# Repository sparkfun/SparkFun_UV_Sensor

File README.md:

SparkFun UV Sensor (Qwiic) - VEML6075
========================================

[*SparkFun UV Sensor (Qwiic) - VEML6075 (SEN-15089)*](https://www.sparkfun.com/products/15089)

Need to apply some sunscreen? SPF 15? SPF 50? SPF 5000? It's time to consult the Qwiic VEML6075 UV sensor!

The **VEML6075** can detect the intensity of UVA (~365nm) and UVB (~330nm) waves. With a quick calculation, those values can be used to generate a standardized **UV index** -- a value from 0 to 11+ which indicates the relative strength of UV irradiance. Seeing a UVI above 6-7? Find some shade, or slather on that sun screen!

The VEML6075 features a simple I<sup>2</sup>C interface, so we stuck it on a [Qwiic](https://www.sparkfun.com/qwiic)-compatible board. This board requires no voltage translation, no figuring out which pin is SDA or SCL; just plug it in and go!

Check out our [SparkFun_VEML6075_Arduino_Library repo](https://github.com/sparkfun/SparkFun_VEML6075_Arduino_Library) for a simple Arduino library -- there's example code to configure the sensor, read its UVA and UVB outputs, and generate a UV index output. Stay safe out there this summer!

SparkFun labored with love to create this code. Feel like supporting open source hardware? 
Buy a [breakout board](https://www.sparkfun.com/products/15089) from SparkFun!

Repository Contents
-------------------

* **/Documents** - Datasheets
* **/Hardware** - Eagle design files (.brd, .sch)
* **/Production** - Production panel files (.brd)

Documentation
--------------
* **[Installing an Arduino Library Guide](https://learn.sparkfun.com/tutorials/installing-an-arduino-library)** - Basic information on how to install an Arduino library.
* **[Library](https://github.com/sparkfun/SparkFun_VEML6075_Arduino_Library)** - Arduino library.
* **[Hookup Guide](https://learn.sparkfun.com/tutorials/qwiic-uv-sensor-veml6075-hookup-guide)** - Basic hookup guide.

Product Versions
----------------
* [SEN-15089](https://www.sparkfun.com/products/15089)- SparkFun Red Version
* [SPX-14748](https://www.sparkfun.com/products/14748)- SparkX Version

License Information
-------------------

This product is _**open source**_! 

Various bits of the code have different licenses applied. Please use, reuse, and modify these files as you see fit. Please maintain attribution to SparkFun Electronics and release any derivative under the same license.

If you have any questions or concerns on licensing, please contact techsupport@sparkfun.com. 

Distributed as-is; no warranty is given.

- Your friends at SparkFun.

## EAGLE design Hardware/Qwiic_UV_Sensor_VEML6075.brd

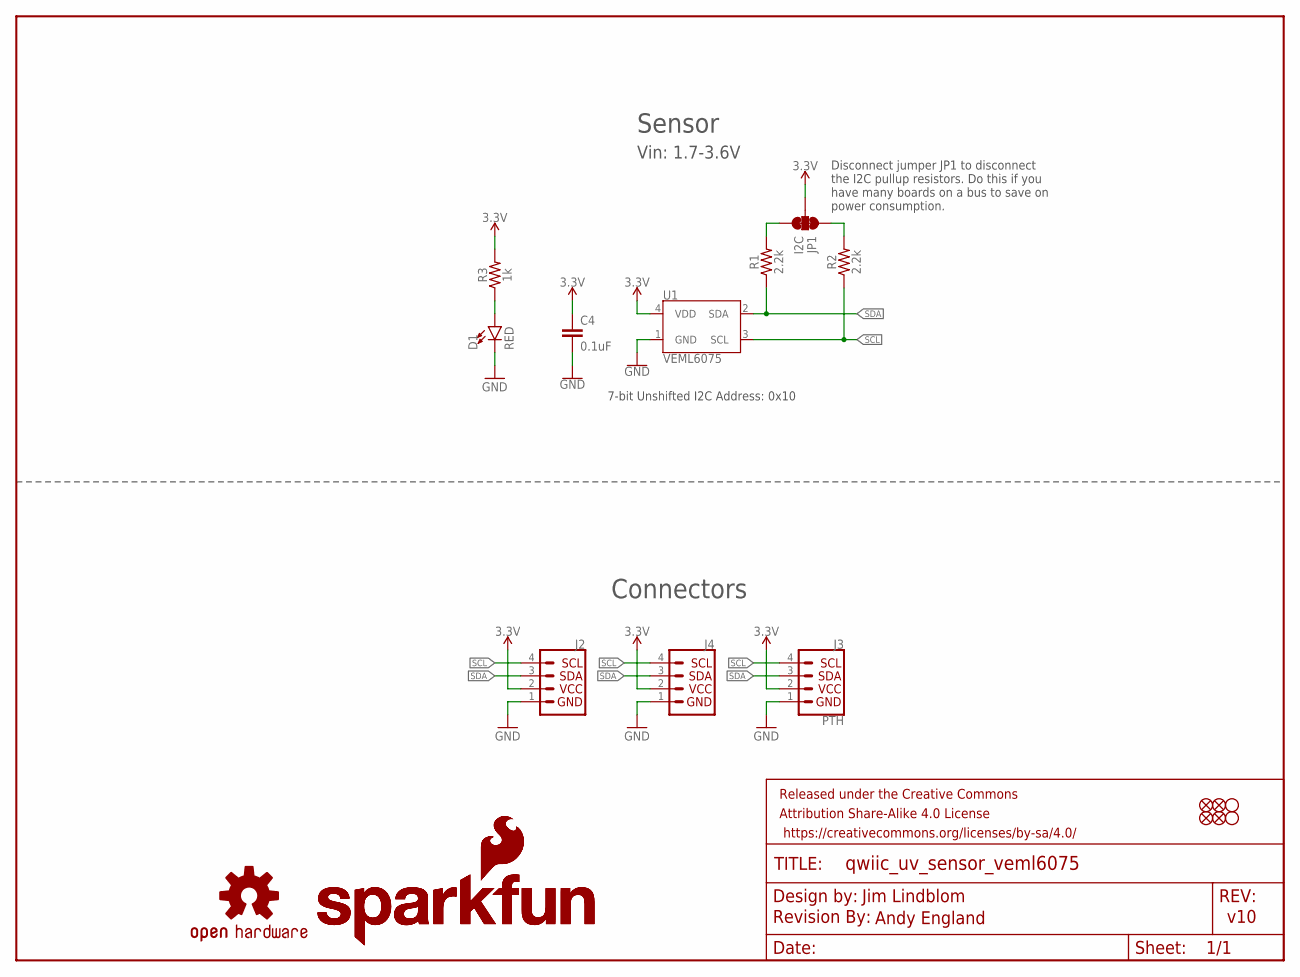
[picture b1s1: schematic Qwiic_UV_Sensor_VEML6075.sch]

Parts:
C4: 0.1uF; 0603
D1: RED; LED-0603
FRAME1: FRAME-LETTER; CREATIVE_COMMONS
J2, J4: QWIIC_CONNECTORJS-1MM; 1X04_1MM_RA
J3: PTH; 1X04_NO_SILK
JP1: I2C; SMT-JUMPER_3_2-NC_TRACE_SILK
JP2, JP5, JP6, JP7: FIDUCIALUFIDUCIAL; MICRO-FIDUCIAL
JP3, JP4: STAND-OFF
LOGO1: OSHW-LOGOMINI; OSHW-LOGO-MINI
LOGO2: REVISION
R1, R2: 2.2k; 0603
R3: 1k; 0603
U1: VEML6075; VEML6075_A3OP
U$1, U$2: SFE_LOGO_NAME_FLAME.1_INCH; SFE_LOGO_NAME_FLAME_.1

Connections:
3.3V: C4.1, J2.2, J3.2 (VCC), J4.2, JP1.2, R3.2, U1.4 (VDD)
GND: C4.2, D1.C, J2.1, J3.1 (GND), J4.1, U1.1 (GND)
unnamed: D1.A, R3.1
unnamed: JP1.3, R1.2
unnamed: JP1.1, R2.2
SCL: J2.4, J3.4 (SCL), J4.4, R2.1, U1.3 (SCL)
SDA: J2.3, J3.3 (SDA), J4.3, R1.1, U1.2 (SDA)

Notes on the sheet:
7-bit Unshifted I2C Address: 0x10
v10
Sensor
Connectors
Jim Lindblom
Andy England
Vin: 1.7-3.6V
Disconnect jumper JP1 to disconnect the I2C pullup resistors. Do this if you have many boards on a bus to save on power consumption.

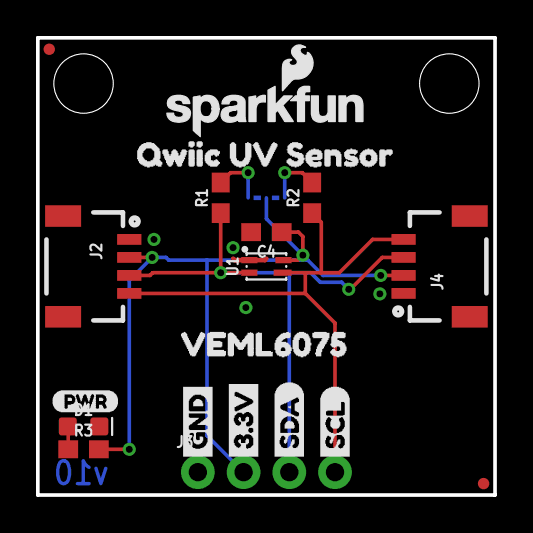
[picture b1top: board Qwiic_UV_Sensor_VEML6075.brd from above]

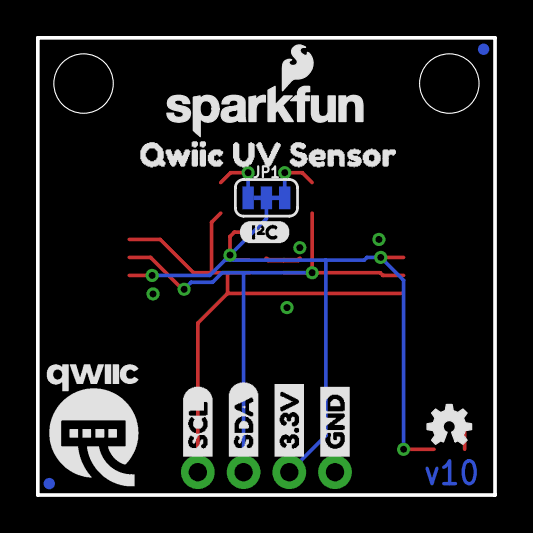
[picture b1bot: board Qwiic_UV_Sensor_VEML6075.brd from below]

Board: 2 copper layers, 25.4 x 25.4 mm, 35 parts (12 on the bottom side), 7 nets.

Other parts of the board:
U$3: QWIIC-LOGO-MEDIUM
U$4, U$22: GND1
U$5, U$11: QWIIC_UV_SENSOR1
U$6: _VEML60750
U$7, U$21: 3#3V2
U$8, U$27: SDA8
U$9, U$26: SCL9
U$10: I_SUPER2_C-()-03
U$16: PWR-()-03

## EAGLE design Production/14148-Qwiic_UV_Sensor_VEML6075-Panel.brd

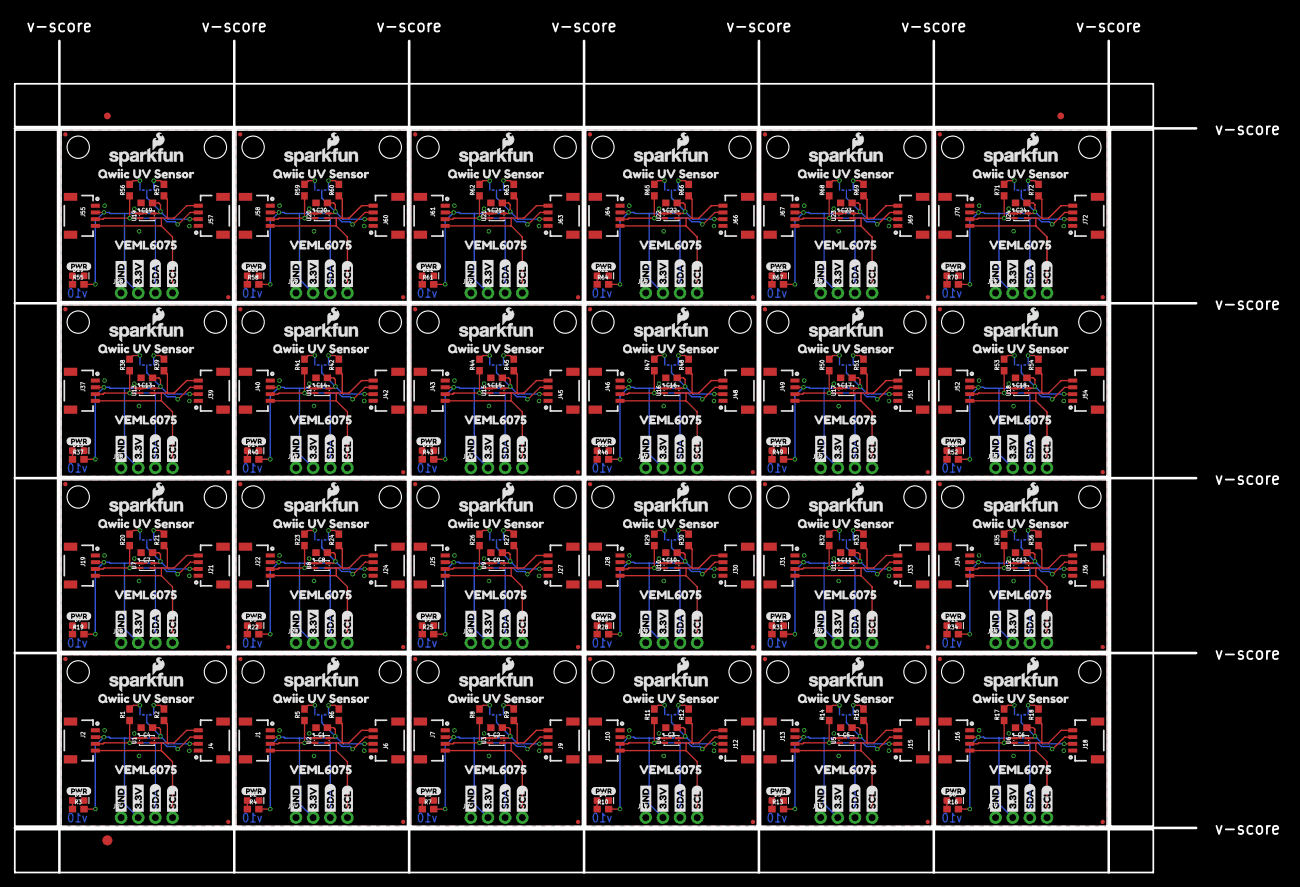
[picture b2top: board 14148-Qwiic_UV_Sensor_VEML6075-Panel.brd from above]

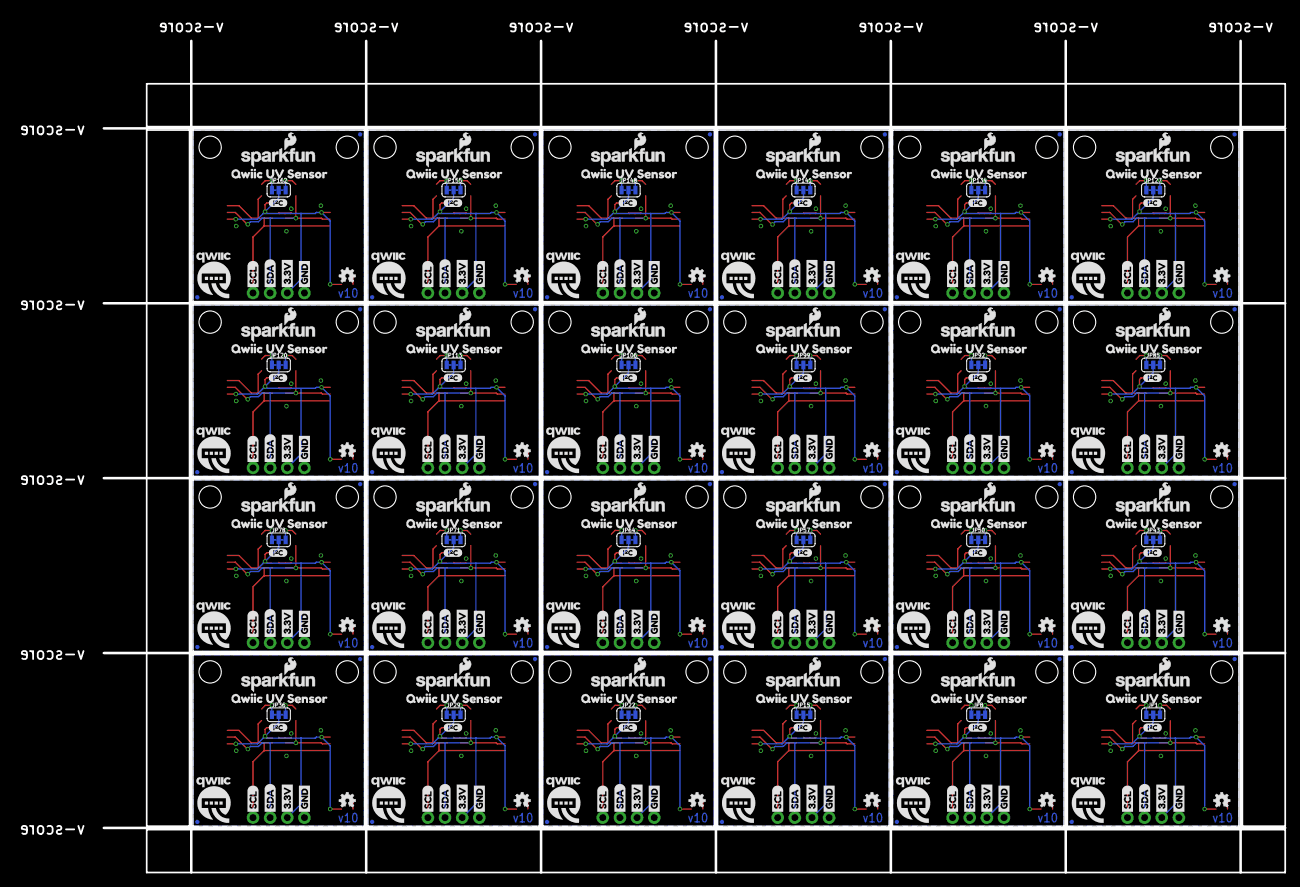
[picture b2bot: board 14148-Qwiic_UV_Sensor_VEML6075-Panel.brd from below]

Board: 2 copper layers, 175.0 x 123.2 mm, 795 parts (288 on the bottom side), 168 nets.

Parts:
C1, C2, C3, C4, C5, C6, C7, C8, C9, C10, C11, C12, C13, C14, C15, C16, C17, C18, C19, C20, C21, C22, C23, C24: 0.1uF; 0603
D1, D2, D3, D4, D5, D6, D7, D8, D9, D10, D11, D12, D13, D14, D15, D16, D17, D18, D19, D20, D21, D22, D23, D24: RED; LED-0603
E$1, E$2: FIDUCIAL-1X2
E$3: FIDUCIAL-1.5X3
J1, J2, J4, J6, J7, J9, J10, J12, J13, J15, J16, J18, J19, J21, J22, J24, J25, J27, J28, J30, J31, J33, J34, J36, J37, J39, J40, J42, J43, J45, J46, J48, J49, J51, J52, J54, J55, J57, J58, J60, J61, J63, J64, J66, J67, J69, J70, J72: 1X04_1MM_RA
J3, J5, J8, J11, J14, J17, J20, J23, J26, J29, J32, J35, J38, J41, J44, J47, J50, J53, J56, J59, J62, J65, J68, J71: PTH; 1X04_NO_SILK
JP1, JP8, JP15, JP22, JP29, JP36, JP43, JP50, JP57, JP64, JP71, JP78, JP85, JP92, JP99, JP106, JP113, JP120, JP127, JP134, JP141, JP148, JP155, JP162: I2C; SMT-JUMPER_3_2-NC_TRACE_SILK
JP2, JP5, JP6, JP7, JP11, JP12, JP13, JP14, JP18, JP19, JP20, JP21, JP25, JP26, JP27, JP28, JP32, JP33, JP34, JP35, JP39, JP40, JP41, JP42, JP46, JP47, JP48, JP49, JP53, JP54, JP55, JP56, JP60, JP61, JP62, JP63, JP67, JP68, JP69, JP70, JP74, JP75, JP76, JP77, JP81, JP82, JP83, JP84, JP88, JP89, JP90, JP91, JP95, JP96, JP97, JP98, JP102, JP103, JP104, JP105, JP109, JP110, JP111, JP112, JP116, JP117, JP118, JP119, JP123, JP124, JP125, JP126, JP130, JP131, JP132, JP133, JP137, JP138, JP139, JP140, JP144, JP145, JP146, JP147, JP151, JP152, JP153, JP154, JP158, JP159, JP160, JP161, JP165, JP166, JP167, JP168: FIDUCIALUFIDUCIAL; MICRO-FIDUCIAL
JP3, JP4, JP9, JP10, JP16, JP17, JP23, JP24, JP30, JP31, JP37, JP38, JP44, JP45, JP51, JP52, JP58, JP59, JP65, JP66, JP72, JP73, JP79, JP80, JP86, JP87, JP93, JP94, JP100, JP101, JP107, JP108, JP114, JP115, JP121, JP122, JP128, JP129, JP135, JP136, JP142, JP143, JP149, JP150, JP156, JP157, JP163, JP164: STAND-OFF
LOGO1, LOGO2, LOGO3, LOGO4, LOGO5, LOGO6, LOGO7, LOGO8, LOGO9, LOGO10, LOGO11, LOGO12, LOGO13, LOGO14, LOGO15, LOGO16, LOGO17, LOGO18, LOGO19, LOGO20, LOGO21, LOGO22, LOGO23, LOGO24: OSHW-LOGOMINI; OSHW-LOGO-MINI
R1, R2, R5, R6, R8, R9, R11, R12, R14, R15, R17, R18, R20, R21, R23, R24, R26, R27, R29, R30, R32, R33, R35, R36, R38, R39, R41, R42, R44, R45, R47, R48, R50, R51, R53, R54, R56, R57, R59, R60, R62, R63, R65, R66, R68, R69, R71, R72: 2.2k; 0603
R3, R4, R7, R10, R13, R16, R19, R22, R25, R28, R31, R34, R37, R40, R43, R46, R49, R52, R55, R58, R61, R64, R67, R70: 1k; 0603
U1, U2, U3, U4, U5, U6, U7, U8, U9, U10, U11, U12, U13, U14, U15, U16, U17, U18, U19, U20, U21, U22, U23, U24: VEML6075; VEML6075_A3OP
U$1, U$2, U$12, U$13, U$33, U$34, U$49, U$50, U$65, U$66, U$81, U$82, U$97, U$98, U$113, U$114, U$129, U$130, U$145, U$146, U$161, U$162, U$177, U$178, U$193, U$194, U$209, U$210, U$225, U$226, U$241, U$242, U$257, U$258, U$273, U$274, U$289, U$290, U$305, U$306, U$321, U$322, U$337, U$338, U$353, U$354, U$369, U$370: SFE_LOGO_NAME_FLAME.1_INCH; SFE_LOGO_NAME_FLAME_.1
U$3, U$14, U$35, U$51, U$67, U$83, U$99, U$115, U$131, U$147, U$163, U$179, U$195, U$211, U$227, U$243, U$259, U$275, U$291, U$307, U$323, U$339, U$355, U$371: QWIIC-LOGO-MEDIUM
U$4, U$17, U$22, U$28, U$37, U$44, U$53, U$60, U$69, U$76, U$85, U$92, U$101, U$108, U$117, U$124, U$133, U$140, U$149, U$156, U$165, U$172, U$181, U$188, U$197, U$204, U$213, U$220, U$229, U$236, U$245, U$252, U$261, U$268, U$277, U$284, U$293, U$300, U$309, U$316, U$325, U$332, U$341, U$348, U$357, U$364, U$373, U$380: GND1
U$5, U$11, U$25, U$32, U$43, U$48, U$59, U$64, U$75, U$80, U$91, U$96, U$107, U$112, U$123, U$128, U$139, U$144, U$155, U$160, U$171, U$176, U$187, U$192, U$203, U$208, U$219, U$224, U$235, U$240, U$251, U$256, U$267, U$272, U$283, U$288, U$299, U$304, U$315, U$320, U$331, U$336, U$347, U$352, U$363, U$368, U$379, U$384: QWIIC_UV_SENSOR1
U$6, U$24, U$42, U$58, U$74, U$90, U$106, U$122, U$138, U$154, U$170, U$186, U$202, U$218, U$234, U$250, U$266, U$282, U$298, U$314, U$330, U$346, U$362, U$378: _VEML60750
U$7, U$15, U$21, U$29, U$36, U$45, U$52, U$61, U$68, U$77, U$84, U$93, U$100, U$109, U$116, U$125, U$132, U$141, U$148, U$157, U$164, U$173, U$180, U$189, U$196, U$205, U$212, U$221, U$228, U$237, U$244, U$253, U$260, U$269, U$276, U$285, U$292, U$301, U$308, U$317, U$324, U$333, U$340, U$349, U$356, U$365, U$372, U$381: 3#3V2
U$8, U$19, U$27, U$30, U$39, U$46, U$55, U$62, U$71, U$78, U$87, U$94, U$103, U$110, U$119, U$126, U$135, U$142, U$151, U$158, U$167, U$174, U$183, U$190, U$199, U$206, U$215, U$222, U$231, U$238, U$247, U$254, U$263, U$270, U$279, U$286, U$295, U$302, U$311, U$318, U$327, U$334, U$343, U$350, U$359, U$366, U$375, U$382: SDA8
U$9, U$18, U$26, U$31, U$38, U$47, U$54, U$63, U$70, U$79, U$86, U$95, U$102, U$111, U$118, U$127, U$134, U$143, U$150, U$159, U$166, U$175, U$182, U$191, U$198, U$207, U$214, U$223, U$230, U$239, U$246, U$255, U$262, U$271, U$278, U$287, U$294, U$303, U$310, U$319, U$326, U$335, U$342, U$351, U$358, U$367, U$374, U$383: SCL9
U$10, U$20, U$40, U$56, U$72, U$88, U$104, U$120, U$136, U$152, U$168, U$184, U$200, U$216, U$232, U$248, U$264, U$280, U$296, U$312, U$328, U$344, U$360, U$376: I_SUPER2_C-()-03
U$16, U$23, U$41, U$57, U$73, U$89, U$105, U$121, U$137, U$153, U$169, U$185, U$201, U$217, U$233, U$249, U$265, U$281, U$297, U$313, U$329, U$345, U$361, U$377: PWR-()-03

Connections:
3.3V: C4.1, J2.2, J3.2, J4.2, JP1.2, R3.2, U1.4
3.3V1: C1.1, J1.2, J5.2, J6.2, JP8.2, R4.2, U2.4
3.3V2: C2.1, J7.2, J8.2, J9.2, JP15.2, R7.2, U3.4
3.3V3: C3.1, J10.2, J11.2, J12.2, JP22.2, R10.2, U4.4
3.3V4: C5.1, J13.2, J14.2, J15.2, JP29.2, R13.2, U5.4
3.3V5: C6.1, J16.2, J17.2, J18.2, JP36.2, R16.2, U6.4
3.3V6: C7.1, J19.2, J20.2, J21.2, JP43.2, R19.2, U7.4
3.3V7: C8.1, J22.2, J23.2, J24.2, JP50.2, R22.2, U8.4
3.3V8: C9.1, J25.2, J26.2, J27.2, JP57.2, R25.2, U9.4
3.3V9: C10.1, J28.2, J29.2, J30.2, JP64.2, R28.2, U10.4
3.3V10: C11.1, J31.2, J32.2, J33.2, JP71.2, R31.2, U11.4
3.3V11: C12.1, J34.2, J35.2, J36.2, JP78.2, R34.2, U12.4
3.3V12: C13.1, J37.2, J38.2, J39.2, JP85.2, R37.2, U13.4
3.3V13: C14.1, J40.2, J41.2, J42.2, JP92.2, R40.2, U14.4
3.3V14: C15.1, J43.2, J44.2, J45.2, JP99.2, R43.2, U15.4
3.3V15: C16.1, J46.2, J47.2, J48.2, JP106.2, R46.2, U16.4
3.3V16: C17.1, J49.2, J50.2, J51.2, JP113.2, R49.2, U17.4
3.3V17: C18.1, J52.2, J53.2, J54.2, JP120.2, R52.2, U18.4
3.3V18: C19.1, J55.2, J56.2, J57.2, JP127.2, R55.2, U19.4
3.3V19: C20.1, J58.2, J59.2, J60.2, JP134.2, R58.2, U20.4
3.3V20: C21.1, J61.2, J62.2, J63.2, JP141.2, R61.2, U21.4
3.3V21: C22.1, J64.2, J65.2, J66.2, JP148.2, R64.2, U22.4
3.3V22: C23.1, J67.2, J68.2, J69.2, JP155.2, R67.2, U23.4
3.3V23: C24.1, J70.2, J71.2, J72.2, JP162.2, R70.2, U24.4
GND: C4.2, D1.C, J2.1, J3.1, J4.1, U1.1
GND1: C1.2, D2.C, J1.1, J5.1, J6.1, U2.1
GND2: C2.2, D3.C, J7.1, J8.1, J9.1, U3.1
GND3: C3.2, D4.C, J10.1, J11.1, J12.1, U4.1
GND4: C5.2, D5.C, J13.1, J14.1, J15.1, U5.1
GND5: C6.2, D6.C, J16.1, J17.1, J18.1, U6.1
GND6: C7.2, D7.C, J19.1, J20.1, J21.1, U7.1
GND7: C8.2, D8.C, J22.1, J23.1, J24.1, U8.1
GND8: C9.2, D9.C, J25.1, J26.1, J27.1, U9.1
GND9: C10.2, D10.C, J28.1, J29.1, J30.1, U10.1
GND10: C11.2, D11.C, J31.1, J32.1, J33.1, U11.1
GND11: C12.2, D12.C, J34.1, J35.1, J36.1, U12.1
GND12: C13.2, D13.C, J37.1, J38.1, J39.1, U13.1
GND13: C14.2, D14.C, J40.1, J41.1, J42.1, U14.1
GND14: C15.2, D15.C, J43.1, J44.1, J45.1, U15.1
GND15: C16.2, D16.C, J46.1, J47.1, J48.1, U16.1
GND16: C17.2, D17.C, J49.1, J50.1, J51.1, U17.1
GND17: C18.2, D18.C, J52.1, J53.1, J54.1, U18.1
GND18: C19.2, D19.C, J55.1, J56.1, J57.1, U19.1
GND19: C20.2, D20.C, J58.1, J59.1, J60.1, U20.1
GND20: C21.2, D21.C, J61.1, J62.1, J63.1, U21.1
GND21: C22.2, D22.C, J64.1, J65.1, J66.1, U22.1
GND22: C23.2, D23.C, J67.1, J68.1, J69.1, U23.1
GND23: C24.2, D24.C, J70.1, J71.1, J72.1, U24.1
unnamed: D2.A, R4.1
unnamed: JP8.3, R5.2
unnamed: D1.A, R3.1
unnamed: JP1.3, R1.2
unnamed: JP1.1, R2.2
unnamed: JP8.1, R6.2
unnamed: D3.A, R7.1
unnamed: JP15.3, R8.2
unnamed: JP15.1, R9.2
unnamed: D4.A, R10.1
unnamed: JP22.3, R11.2
unnamed: JP22.1, R12.2
unnamed: D5.A, R13.1
unnamed: JP29.3, R14.2
unnamed: JP29.1, R15.2
unnamed: D6.A, R16.1
unnamed: JP36.3, R17.2
unnamed: JP36.1, R18.2
unnamed: D7.A, R19.1
unnamed: JP43.3, R20.2
unnamed: JP43.1, R21.2
unnamed: D8.A, R22.1
unnamed: JP50.3, R23.2
unnamed: JP50.1, R24.2
unnamed: D9.A, R25.1
unnamed: JP57.3, R26.2
unnamed: JP57.1, R27.2
unnamed: D10.A, R28.1
unnamed: JP64.3, R29.2
unnamed: JP64.1, R30.2
unnamed: D11.A, R31.1
unnamed: JP71.3, R32.2
unnamed: JP71.1, R33.2
unnamed: D12.A, R34.1
unnamed: JP78.3, R35.2
unnamed: JP78.1, R36.2
unnamed: D13.A, R37.1
unnamed: JP85.3, R38.2
unnamed: JP85.1, R39.2
unnamed: D14.A, R40.1
unnamed: JP92.3, R41.2
unnamed: JP92.1, R42.2
unnamed: D15.A, R43.1
unnamed: JP99.3, R44.2
unnamed: JP99.1, R45.2
unnamed: D16.A, R46.1
unnamed: JP106.3, R47.2
unnamed: JP106.1, R48.2
unnamed: D17.A, R49.1
unnamed: JP113.3, R50.2
unnamed: JP113.1, R51.2
unnamed: D18.A, R52.1
unnamed: JP120.3, R53.2
unnamed: JP120.1, R54.2
unnamed: D19.A, R55.1
unnamed: JP127.3, R56.2
unnamed: JP127.1, R57.2
unnamed: D20.A, R58.1
unnamed: JP134.3, R59.2
unnamed: JP134.1, R60.2
unnamed: D21.A, R61.1
unnamed: JP141.3, R62.2
unnamed: JP141.1, R63.2
unnamed: D22.A, R64.1
unnamed: JP148.3, R65.2
unnamed: JP148.1, R66.2
unnamed: D23.A, R67.1
unnamed: JP155.3, R68.2
unnamed: JP155.1, R69.2
unnamed: D24.A, R70.1
unnamed: JP162.3, R71.2
unnamed: JP162.1, R72.2
SCL: J2.4, J3.4, J4.4, R2.1, U1.3
SCL1: J1.4, J5.4, J6.4, R6.1, U2.3
SCL2: J7.4, J8.4, J9.4, R9.1, U3.3
SCL3: J10.4, J11.4, J12.4, R12.1, U4.3
SCL4: J13.4, J14.4, J15.4, R15.1, U5.3
SCL5: J16.4, J17.4, J18.4, R18.1, U6.3
SCL6: J19.4, J20.4, J21.4, R21.1, U7.3
SCL7: J22.4, J23.4, J24.4, R24.1, U8.3
SCL8: J25.4, J26.4, J27.4, R27.1, U9.3
SCL9: J28.4, J29.4, J30.4, R30.1, U10.3
SCL10: J31.4, J32.4, J33.4, R33.1, U11.3
SCL11: J34.4, J35.4, J36.4, R36.1, U12.3
SCL12: J37.4, J38.4, J39.4, R39.1, U13.3
SCL13: J40.4, J41.4, J42.4, R42.1, U14.3
SCL14: J43.4, J44.4, J45.4, R45.1, U15.3
SCL15: J46.4, J47.4, J48.4, R48.1, U16.3
SCL16: J49.4, J50.4, J51.4, R51.1, U17.3
SCL17: J52.4, J53.4, J54.4, R54.1, U18.3
SCL18: J55.4, J56.4, J57.4, R57.1, U19.3
SCL19: J58.4, J59.4, J60.4, R60.1, U20.3
SCL20: J61.4, J62.4, J63.4, R63.1, U21.3
SCL21: J64.4, J65.4, J66.4, R66.1, U22.3
SCL22: J67.4, J68.4, J69.4, R69.1, U23.3
SCL23: J70.4, J71.4, J72.4, R72.1, U24.3
SDA: J2.3, J3.3, J4.3, R1.1, U1.2
SDA1: J1.3, J5.3, J6.3, R5.1, U2.2
SDA2: J7.3, J8.3, J9.3, R8.1, U3.2
SDA3: J10.3, J11.3, J12.3, R11.1, U4.2
SDA4: J13.3, J14.3, J15.3, R14.1, U5.2
SDA5: J16.3, J17.3, J18.3, R17.1, U6.2
SDA6: J19.3, J20.3, J21.3, R20.1, U7.2
SDA7: J22.3, J23.3, J24.3, R23.1, U8.2
SDA8: J25.3, J26.3, J27.3, R26.1, U9.2
SDA9: J28.3, J29.3, J30.3, R29.1, U10.2
SDA10: J31.3, J32.3, J33.3, R32.1, U11.2
SDA11: J34.3, J35.3, J36.3, R35.1, U12.2
SDA12: J37.3, J38.3, J39.3, R38.1, U13.2
SDA13: J40.3, J41.3, J42.3, R41.1, U14.2
SDA14: J43.3, J44.3, J45.3, R44.1, U15.2
SDA15: J46.3, J47.3, J48.3, R47.1, U16.2
SDA16: J49.3, J50.3, J51.3, R50.1, U17.2
SDA17: J52.3, J53.3, J54.3, R53.1, U18.2
SDA18: J55.3, J56.3, J57.3, R56.1, U19.2
SDA19: J58.3, J59.3, J60.3, R59.1, U20.2
SDA20: J61.3, J62.3, J63.3, R62.1, U21.2
SDA21: J64.3, J65.3, J66.3, R65.1, U22.2
SDA22: J67.3, J68.3, J69.3, R68.1, U23.2
SDA23: J70.3, J71.3, J72.3, R71.1, U24.2

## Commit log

2018-11-12 pre review changes
2018-11-13 post checklist changes
2018-11-14 Created panel v10

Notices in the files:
parts and their libraries:
SparkFun-Aesthetics: Licensing: Creative Commons ShareAlike 4.0 International - https://creativecommons.org/licenses/by-sa/4.0
SparkFun-Aesthetics: Released under the Creative Commons Attribution Share-Alike 4.0 License
SparkFun-Aesthetics: https://creativecommons.org/licenses/by-sa/4.0
